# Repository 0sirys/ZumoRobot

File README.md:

# ZumoRobot
Robot zumo ToF &amp; IR Sensors, buck-converter, 2X 6VDC motors, ESP32-S3-WROOM-1U, Lipo Battery 2S.

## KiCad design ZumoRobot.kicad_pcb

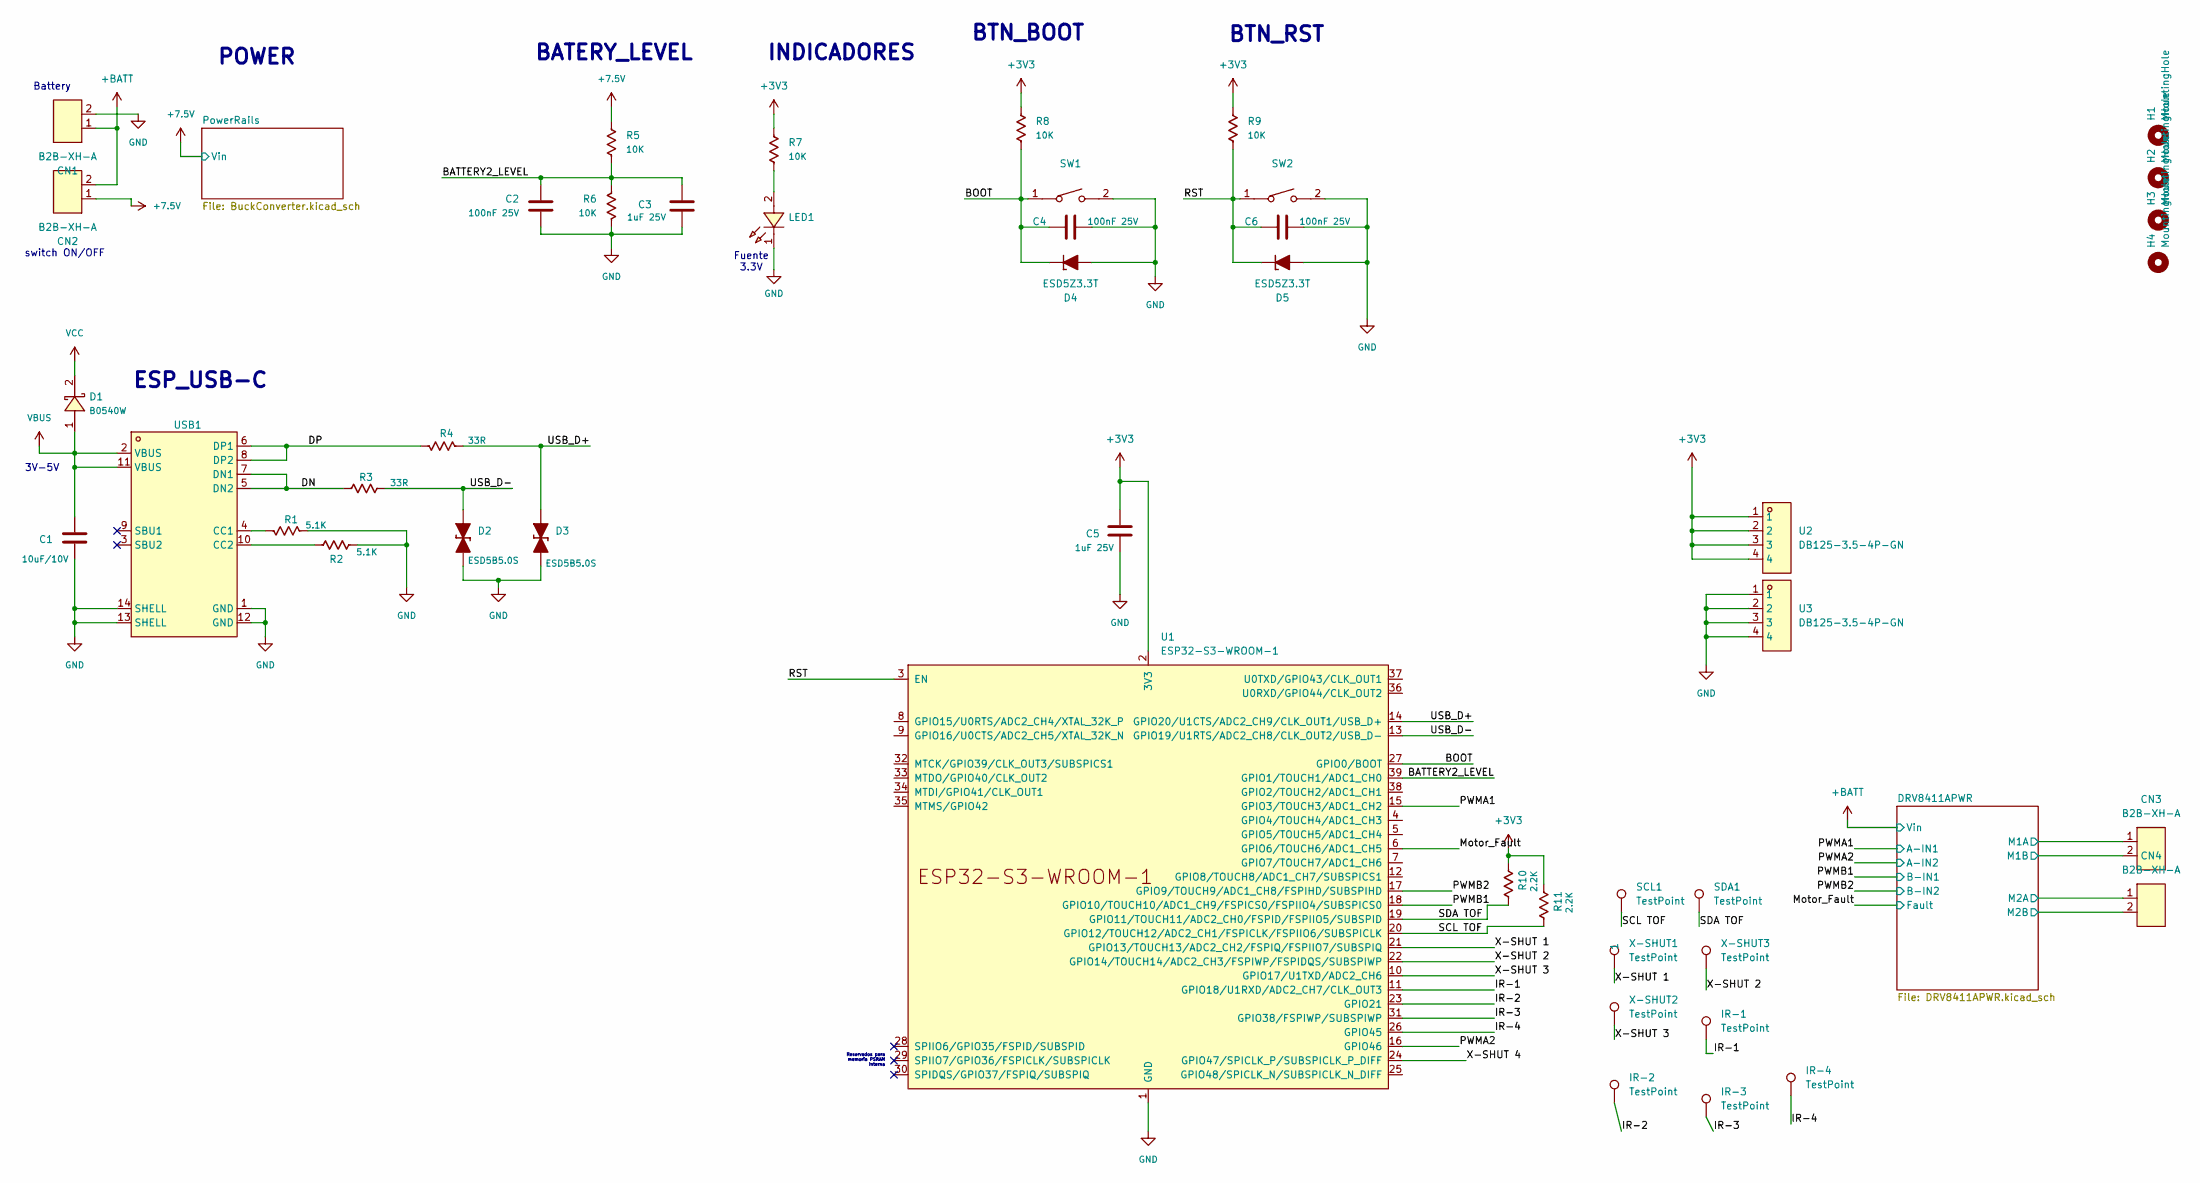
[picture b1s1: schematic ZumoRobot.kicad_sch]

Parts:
C1: 10uF/10V; C_0805_2012Metric; LCSC Part C326595
C2, C4, C6: 100nF 25V; C_0603_1608Metric; LCSC Part C14663
C3, C5: 1uF 25V; C_0805_2012Metric; LCSC Part 5370002
CN1, CN2, CN3, CN4: B2B-XH-A; CONN-TH_B2B-XH-A-LF-SN; MPN B2B-XH-A(LF)(SN); LCSC Part C158012
D1: B0540W; SOD-123_L2.7-W1.6-LS3.7-FD; MPN B0540W; LCSC Part C7420325
D2, D3: ESD5B5.0S; D_SOD-523; LCSC Part C2936975
D4, D5: ESD5Z3.3T; D_SOD-523; LCSC Part C61148
H1, H2, H3, H4: MountingHole; MountingHole_2.5mm
IR-1, IR-2, IR-3, IR-4: TestPoint; TestPoint-1.25mm
LED1: XL-1608SURC-06; LED0603-RD_RED; MPN XL-1608SURC-06; LCSC Part C965799
R1, R2: 5.1K; R_0603_1608Metric; LCSC Part C125891
R3, R4: 33R; R_0603_1608Metric; LCSC Part C108407
R5, R6, R7, R8, R9: 10K; R_0603_1608Metric; LCSC Part C860067
R10, R11: 2.2K; R_0603_1608Metric; LCSC Part C125891
SCL1: TestPoint; TestPoint-1.25mm
SDA1: TestPoint; TestPoint-1.25mm
SW1, SW2: TS-1088-AR02016; SW-SMD_L3.9-W3.0-P4.45; MPN TS-1088-AR02016; LCSC Part C720477
U1: ESP32-S3-WROOM-1; ESP32-S3-WROOM-1U; LCSC Part C2913202
U2, U3: DB125-3.5-4P-GN; CONN-TH_DB125-3.5-4P-GN; MPN DB125-3.5-4P-GN-S; LCSC Part C2757925
USB1: TYPE-C 16PIN 2MD; USB-C-SMD_TYPE-C-6PIN-2MD-073; MPN TYPE-C 16PIN 2MD(073); LCSC Part C2765186
X-SHUT1, X-SHUT2, X-SHUT3: TestPoint; TestPoint-1.25mm

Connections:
+3V3: C5.1, R7.1, R8.1, R9.1, R10.2, R11.2, U1.2 (3V3), U2.1, U2.2, U2.3, U2.4; also elsewhere on the board
+7.5V: CN2.1, R5.1; also elsewhere on the board
+BATT: CN1.1, CN2.2; also elsewhere on the board
/BATTERY2_LEVEL: C2.1, C3.1, R5.2, R6.1, U1.39 (GPIO1/TOUCH1/ADC1_CH0)
/BOOT: C4.1, D4.1 (K), R8.2, SW1.1, U1.27 (GPIO0/BOOT)
/DN: R3.1, USB1.5 (DN2), USB1.7 (DN1)
/DP: R4.1, USB1.6 (DP1), USB1.8 (DP2)
/DRV8411APWR/M1A: CN3.1; also elsewhere on the board
/DRV8411APWR/M1B: CN3.2; also elsewhere on the board
/DRV8411APWR/M2A: CN4.1; also elsewhere on the board
/DRV8411APWR/M2B: CN4.2; also elsewhere on the board
/IR-1: IR-1.1 (1_1), U1.11 (GPIO18/U1RXD/ADC2_CH7/CLK_OUT3)
/IR-2: IR-2.1 (1_1), U1.23 (GPIO21)
/IR-3: IR-3.1 (1_1), U1.31 (GPIO38/FSPIWP/SUBSPIWP)
/IR-4: IR-4.1 (1_1), U1.26 (GPIO45)
/Motor_Fault: U1.6 (GPIO6/TOUCH6/ADC1_CH5); also elsewhere on the board
/PWMA1: U1.15 (GPIO3/TOUCH3/ADC1_CH2); also elsewhere on the board
/PWMA2: U1.16 (GPIO46); also elsewhere on the board
/PWMB1: U1.18 (GPIO10/TOUCH10/ADC1_CH9/FSPICS0/FSPIIO4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); also elsewhere on the board
/PWMB2: U1.17 (GPIO9/TOUCH9/ADC1_CH8/FSPIHD/SUBSPIHD); also elsewhere on the board
/RST: C6.1, D5.1 (K), R9.2, SW2.1, U1.3 (EN)
/SCL TOF: R11.1, SCL1.1 (1_1), U1.20 (GPIO12/TOUCH12/ADC2_CH1/FSPICLK/FSPIIO6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)
/SDA TOF: R10.1, SDA1.1 (1_1), U1.19 (GPIO11/TOUCH11/ADC2_CH0/FSPID/FSPIIO5/S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)
/USB_D+: D3.2 (A), R4.2, U1.14 (GPIO20/U1CTS/ADC2_CH9/CLK_OUT1/USB_D+)
/USB_D-: D2.2 (A), R3.2, U1.13 (GPIO19/U1RTS/ADC2_CH8/CLK_OUT2/USB_D-)
/X-SHUT 1: U1.21 (GPIO13/TOUCH13/ADC2_CH2/FSPIQ/FSPIIO7/S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), X-SHUT1.1 (1_1)
/X-SHUT 2: U1.22 (GPIO14/TOUCH14/ADC2_CH3/FSPIWP/FSPIDQS/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), X-SHUT3.1 (1_1)
/X-SHUT 3: U1.10 (GPIO17/U1TXD/ADC2_CH6), X-SHUT2.1 (1_1)
/X-SHUT 4: U1.24 (GPIO47/SPICLK_P/SUBSPICLK_P_DIFF)
GND: C1.2, C2.2, C3.2, C4.2, C5.2, C6.2, CN1.2, D2.1 (K), D3.1 (K), D4.2 (A), D5.2 (A), LED1.1, R1.2, R2.2, R6.2, SW1.2, SW2.2, U1.1 (GND), U1.40 (GND), U1.41 (GND), U3.1, U3.2, U3.3, U3.4, USB1.1 (GND), USB1.12 (GND), USB1.13 (SHELL), USB1.14 (SHELL); also elsewhere on the board
unnamed: LED1.2, R7.2
unnamed: R1.1, USB1.4 (CC1)
unnamed: R2.1, USB1.10 (CC2)
VBUS: C1.1, D1.1, USB1.2 (VBUS), USB1.11 (VBUS)
VCC: D1.2; also elsewhere on the board

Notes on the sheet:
Fuente 3.3V
POWER
BATERY_LEVEL
Battery
INDICADORES
BTN_BOOT
ESP_USB-C
BTN_RST
switch ON/OFF
Reservados para memoria PSRAM Interna
3V-5V

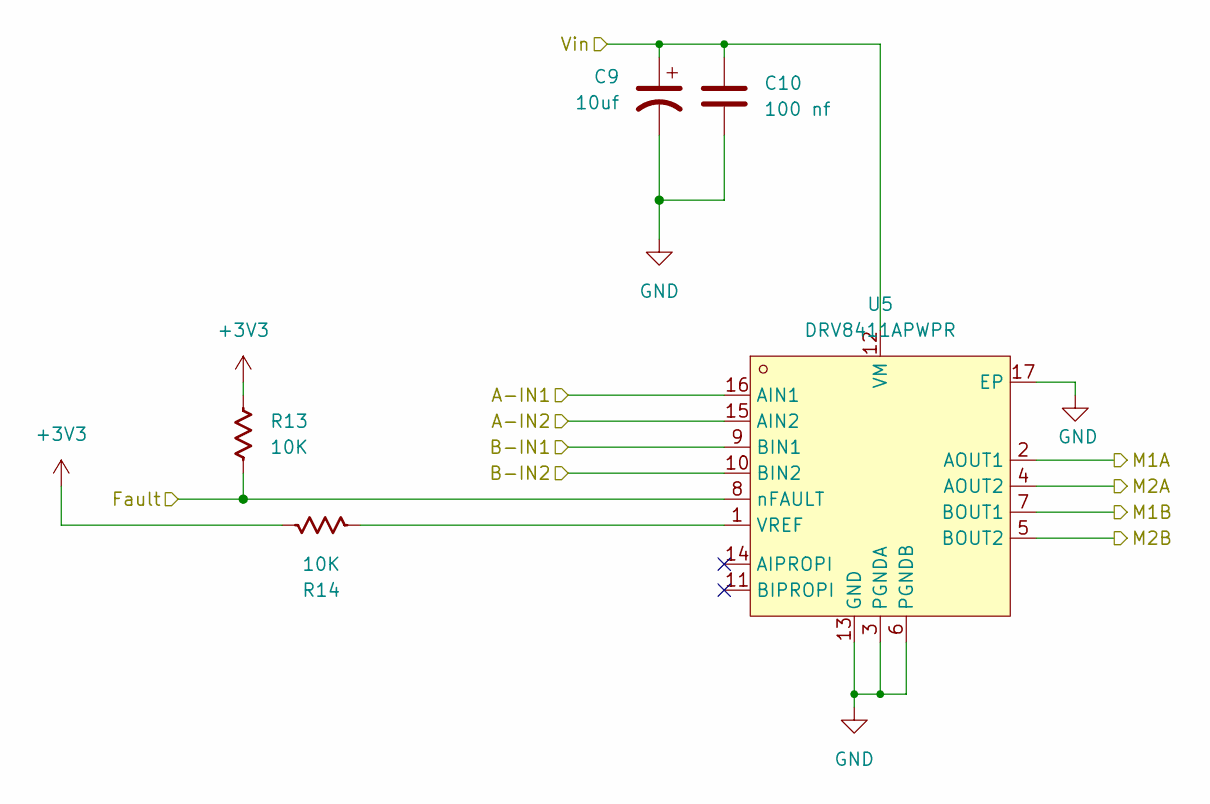
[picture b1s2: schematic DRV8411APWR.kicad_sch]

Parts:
C9: 10uf; CP_Elec_6.3x5.4; LCSC Part C326595
C10: 100 nf; C_0603_1608Metric; LCSC Part C14663
R13, R14: 10K; R_0603_1608Metric; LCSC Part C860067
U5: DRV8411APWPR; HTSSOP-16_L5.0-W4.4-P0.65-LS6.4-TL-EP-1; MPN DRV8411APWPR; LCSC Part C22428260

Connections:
+3V3: R13.1, R14.1; also elsewhere on the board
+BATT: C9.1, C10.1, U5.12 (VM); also elsewhere on the board
/DRV8411APWR/M1A: U5.2 (AOUT1); also elsewhere on the board
/DRV8411APWR/M1B: U5.7 (BOUT1); also elsewhere on the board
/DRV8411APWR/M2A: U5.4 (AOUT2); also elsewhere on the board
/DRV8411APWR/M2B: U5.5 (BOUT2); also elsewhere on the board
/Motor_Fault: R13.2, U5.8 (nFAULT); also elsewhere on the board
/PWMA1: U5.16 (AIN1); also elsewhere on the board
/PWMA2: U5.15 (AIN2); also elsewhere on the board
/PWMB1: U5.9 (BIN1); also elsewhere on the board
/PWMB2: U5.10 (BIN2); also elsewhere on the board
GND: C9.2, C10.2, U5.3 (PGNDA), U5.6 (PGNDB), U5.13 (GND), U5.17 (EP); also elsewhere on the board
unnamed: R14.2, U5.1 (VREF)

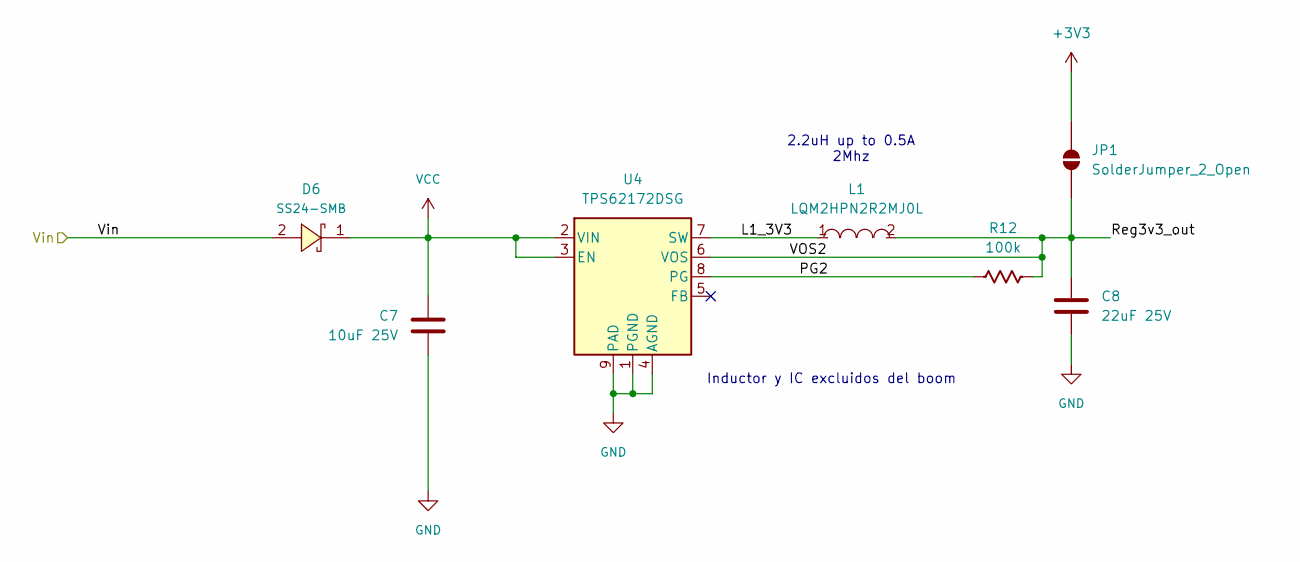
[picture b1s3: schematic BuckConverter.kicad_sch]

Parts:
C7: 10uF 25V; C_1210_3225Metric; LCSC Part C577292
C8: 22uF 25V; C_0805_2012Metric; LCSC Part C602037
D6: SS24-SMB; SMB_L4.3-W3.6-LS5.3-RD; MPN SS24-SMB; LCSC Part C908683
JP1: SolderJumper_2_Open; Jumper_2_NO
L1: LQM2HPN2R2MJ0L; L1008; MPN LQM2HPN2R2MJ0L; LCSC Part C113101
R12: 100k; R_0603_1608Metric; LCSC Part C122538
U4: TPS62172DSG; WSON-8-1EP_2x2mm_P0.5mm_EP0.9x1.6mm_ThermalVias; LCSC Part C59873

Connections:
+3V3: JP1.2 (B); also elsewhere on the board
+7.5V: D6.2; also elsewhere on the board
/PowerRails/L1_3V3: L1.1, U4.7 (SW)
/PowerRails/PG2: R12.1, U4.8 (PG)
/PowerRails/Reg3v3_out: C8.1, JP1.1 (A), L1.2, R12.2, U4.6 (VOS)
GND: C7.2, C8.2, U4.1 (PGND), U4.4 (AGND), U4.9 (PAD); also elsewhere on the board
VCC: C7.1, D6.1, U4.2 (VIN), U4.3 (EN); also elsewhere on the board

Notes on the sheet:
2.2uH up to 0.5A 2Mhz
Inductor y IC excluidos del boom

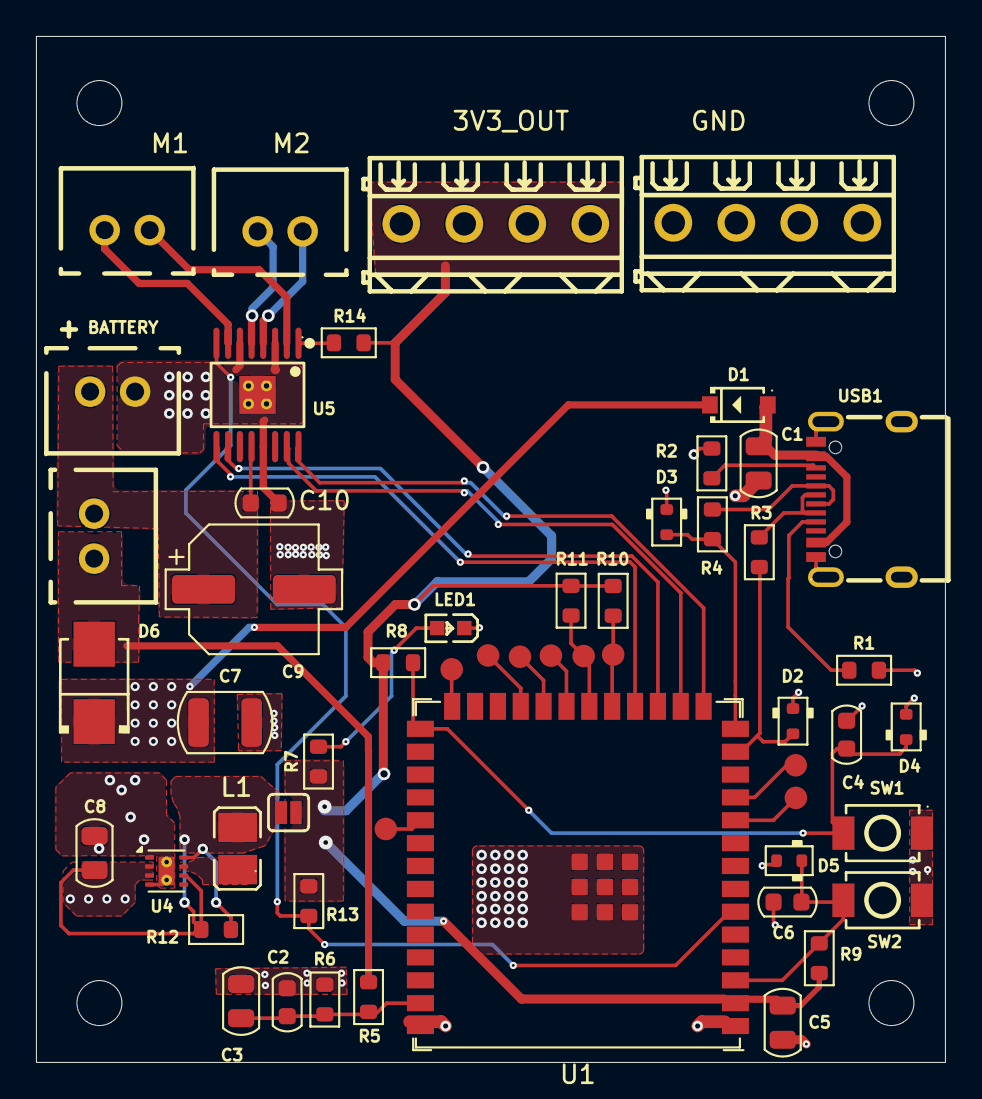
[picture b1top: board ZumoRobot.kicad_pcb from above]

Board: 2 copper layers, 50.5 x 57.0 mm, 58 parts (0 on the bottom side), 38 nets.

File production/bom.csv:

Designator,Footprint,Quantity,Value,LCSC Part #
C1,0805,1,10uF/10V,C326595
C10,0603,1,C_0603,
"C2, C4, C6",0603,3,100nF 25V,C14663
"C3, C5",0805,2,1uF 25V,5370002
C7,1210,1,10uF 25V,C577292
C8,0805,1,22uF 25V,C602037
C9,CP_Elec_6.3x5.4,1,CP_SMD_D6.3mm_H5.4mm,
"CN1, CN2, CN3, CN4",CONN-TH_B2B-XH-A-LF-SN,4,B2B-XH-A,C158012
D1,SOD-123_L2.7-W1.6-LS3.7-FD,1,B0540W,C7420325
"D2, D3",D_SOD-523,2,ESD5B5.0S,C2936975
"D4, D5",D_SOD-523,2,ESD5Z3.3T,C61148
D6,SMB_L4.3-W3.6-LS5.3-RD,1,SS24-SMB,C908683
"IR-1, IR-2, IR-3, IR-4, SCL1, SDA1, X-SHUT1, X-SHUT2, X-SHUT3",TestPoint-1.25mm,9,TestPoint,
L1,L1008,1,LQM2HPN2R2MJ0L,C113101
LED1,LED0603-RD_RED,1,XL-1608SURC-06,C965799
"R1, R2",0603,2,5.1K,C125891
"R10, R11",0603,2,2.2K,C125891
R12,0603,1,100k,C122538
R13,0603,1,10K,C122538
R14,0603,1,10K,
"R3, R4",0603,2,33R,C108407
"R5, R6, R7, R8, R9",0603,5,10K,C860067
"SW1, SW2",SW-SMD_L3.9-W3.0-P4.45,2,TS-1088-AR02016,C720477
U1,ESP32-S3-WROOM-1U,1,ESP32-S3-WROOM-1,
"U2, U3",CONN-TH_DB125-3.5-4P-GN,2,DB125-3.5-4P-GN,C2757925
U5,HTSSOP-16_L5.0-W4.4-P0.65-LS6.4-TL-EP-1,1,DRV8411APWPR,C22428260
USB1,USB-C-SMD_TYPE-C-6PIN-2MD-073,1,TYPE-C 16PIN 2MD,C2765186
